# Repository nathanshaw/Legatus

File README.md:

# Legatus Hardware

This repo contains the PCB layout and schematic files for the Legatus genus.
Legatus is one of three genera developed for the Acropolis family of soundscape augmentation artefacts. Legatus specialises in loudspeaker-based cochlear soundscape augmentation.

The files were created within EAGLE CAD

The Legatus genus firmware is contained in this repo: https://github.com/nathanshaw/unified_hss_firmware

More information about this project can be found here: https://nathanvillicanashaw.com/archive
The Explorator genus can be found here: https://github.com/nathanshaw/explorator
The Speculator genus can be found here: https://github.com/nathanshaw/speculator

The following PCB design is included in this repo:
----------------------------------------------------

### Legatus major
    86mm diameter
    1x Teensy 3.2 Microcontroller
    1x power switch
    6x firmware control switches
    2x firmware control potentiometers
    10x WS2813 NeoPixel LEDs
    2x VEML 6030 Ambient Light Sensors
    1x 5v voltage regulator (D24V50F5): https://www.pololu.com/product/2851
    1x SHTC3 Temperature and Humidity Sensor
    2x onboard 18500 LiPo Batteries
    1x button controller IC
    1x audio amplifier breakout PCB
    1x SGTL5000 Breakout PCB
    2x TDK ICS-43434 MEMs microphone

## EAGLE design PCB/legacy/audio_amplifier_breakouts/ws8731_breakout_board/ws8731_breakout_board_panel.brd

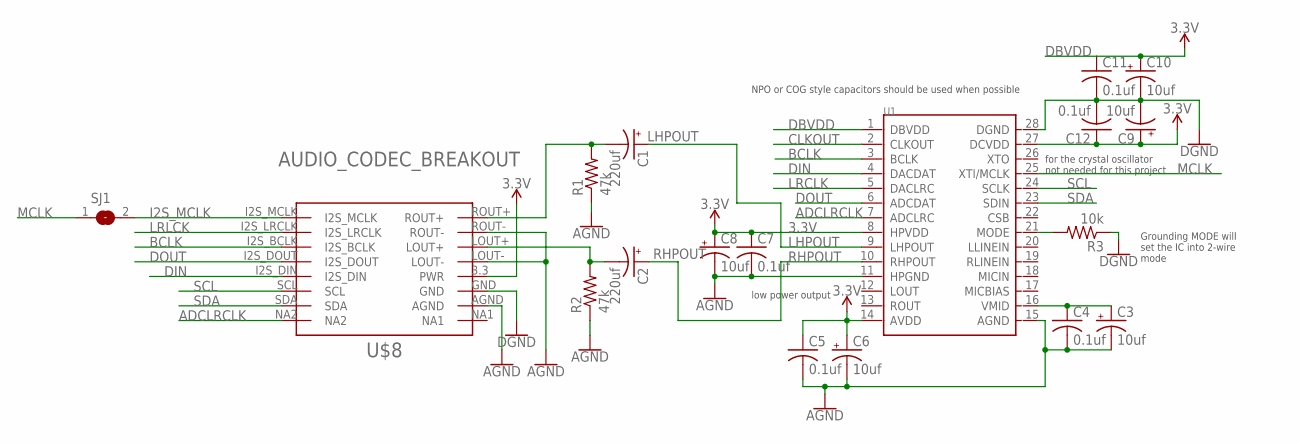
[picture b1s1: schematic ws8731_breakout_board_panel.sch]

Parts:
C1, C2: 220uf; PANASONIC_D
C3, C6, C8, C9, C10: 10uf; 153CLV-0505
C4, C5, C7, C11, C12: 0.1uf; C0805K
R1, R2: 47k; R0805
R3: 10k; R0805
SJ1: SJ
U1: CODECODER-WM8731SEDS/V(SSOP28); SSOP28-0.65-10.2X5.2MM
U$8: AUDIO_CODEC_BREAKOUT; HSS_CODEC_BREAKOUT

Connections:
3.3V: C5.1, C6.+, C7.1, C8.+, C9.+, C12.1, U1.8 (HPVDD), U1.14 (AVDD), U1.27 (DCVDD), U$8.3.3 (PWR)
ADCLRCLK: U1.7 (ADCLRC), U$8.NA2
AGND: C3.-, C4.2, C5.2, C6.-, C7.2, C8.-, R1.1, R2.1, U1.11 (HPGND), U1.15 (AGND), U$8.AGND, U$8.LOUT-, U$8.ROUT-
BCLK: U1.3 (BCLK), U$8.I2S_BCLK
CLKOUT: U1.2 (CLKOUT)
DBVDD: C10.+, C11.1, U1.1 (DBVDD)
DGND: C9.-, C10.-, C11.2, C12.2, R3.1, U1.28 (DGND)
DIN: U1.4 (DACDAT), U$8.I2S_DIN
DOUT: U1.6 (ADCDAT), U$8.I2S_DOUT
GND: U$8.GND
I2S_MCLK: SJ1.2, U$8.I2S_MCLK
LHPOUT: C1.+, U1.9 (LHPOUT)
LRCLK: U1.5 (DACLRC)
LRLCK: U$8.I2S_LRCLK
MCLK: SJ1.1, U1.25 (XTI/MCLK)
MODE: R3.2, U1.21 (MODE)
unnamed: C1.-, R1.2, U$8.ROUT+
unnamed: C2.-, R2.2, U$8.LOUT+
unnamed: C3.+, C4.1, U1.16 (VMID)
RHPOUT: C2.+, U1.10 (RHPOUT)
SCL: U1.24 (SCLK), U$8.SCL
SDA: U1.23 (SDIN), U$8.SDA

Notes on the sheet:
low power output
NPO or COG style capacitors should be used when possible
Grounding MODE will set the IC into 2-wire mode
for the crystal oscillator not needed for this project

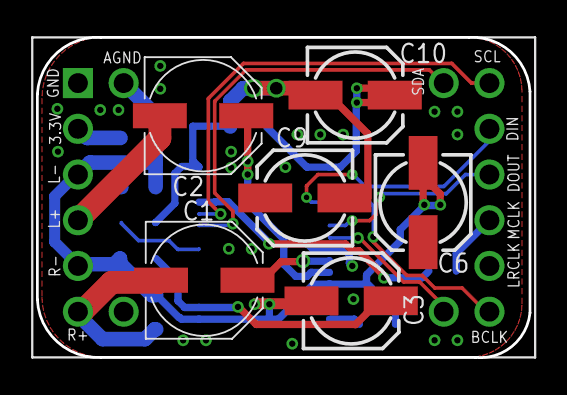
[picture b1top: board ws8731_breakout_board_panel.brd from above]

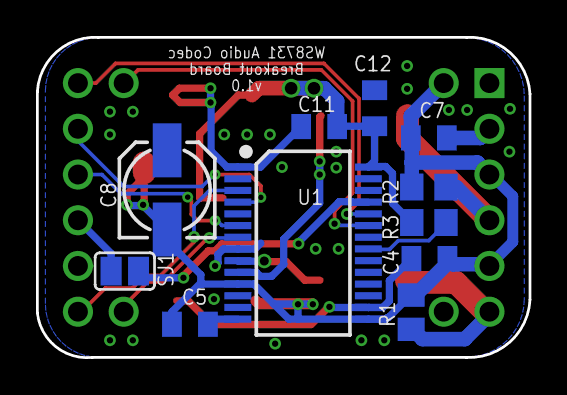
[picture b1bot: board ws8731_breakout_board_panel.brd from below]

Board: 2 copper layers, 27.4 x 17.8 mm, 18 parts (11 on the bottom side), 18 nets.

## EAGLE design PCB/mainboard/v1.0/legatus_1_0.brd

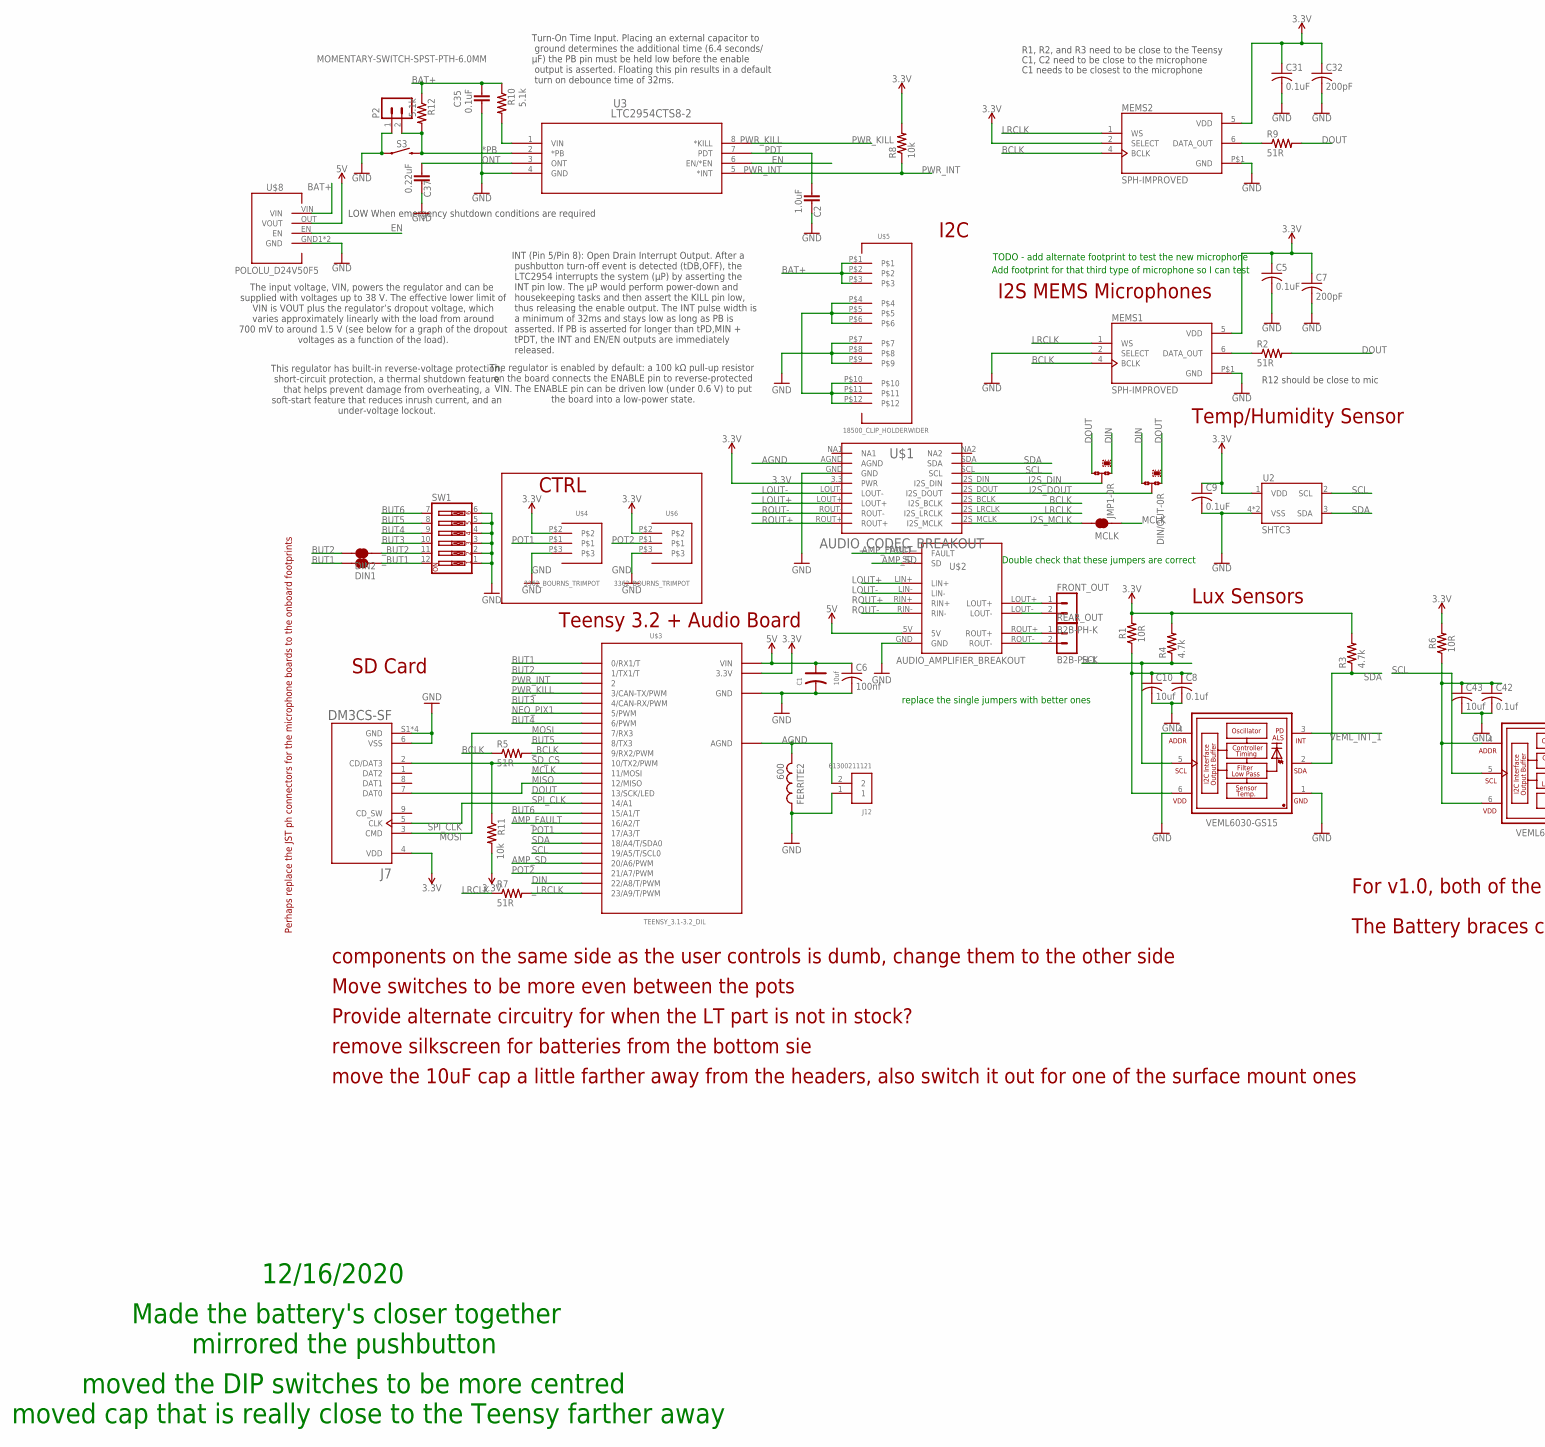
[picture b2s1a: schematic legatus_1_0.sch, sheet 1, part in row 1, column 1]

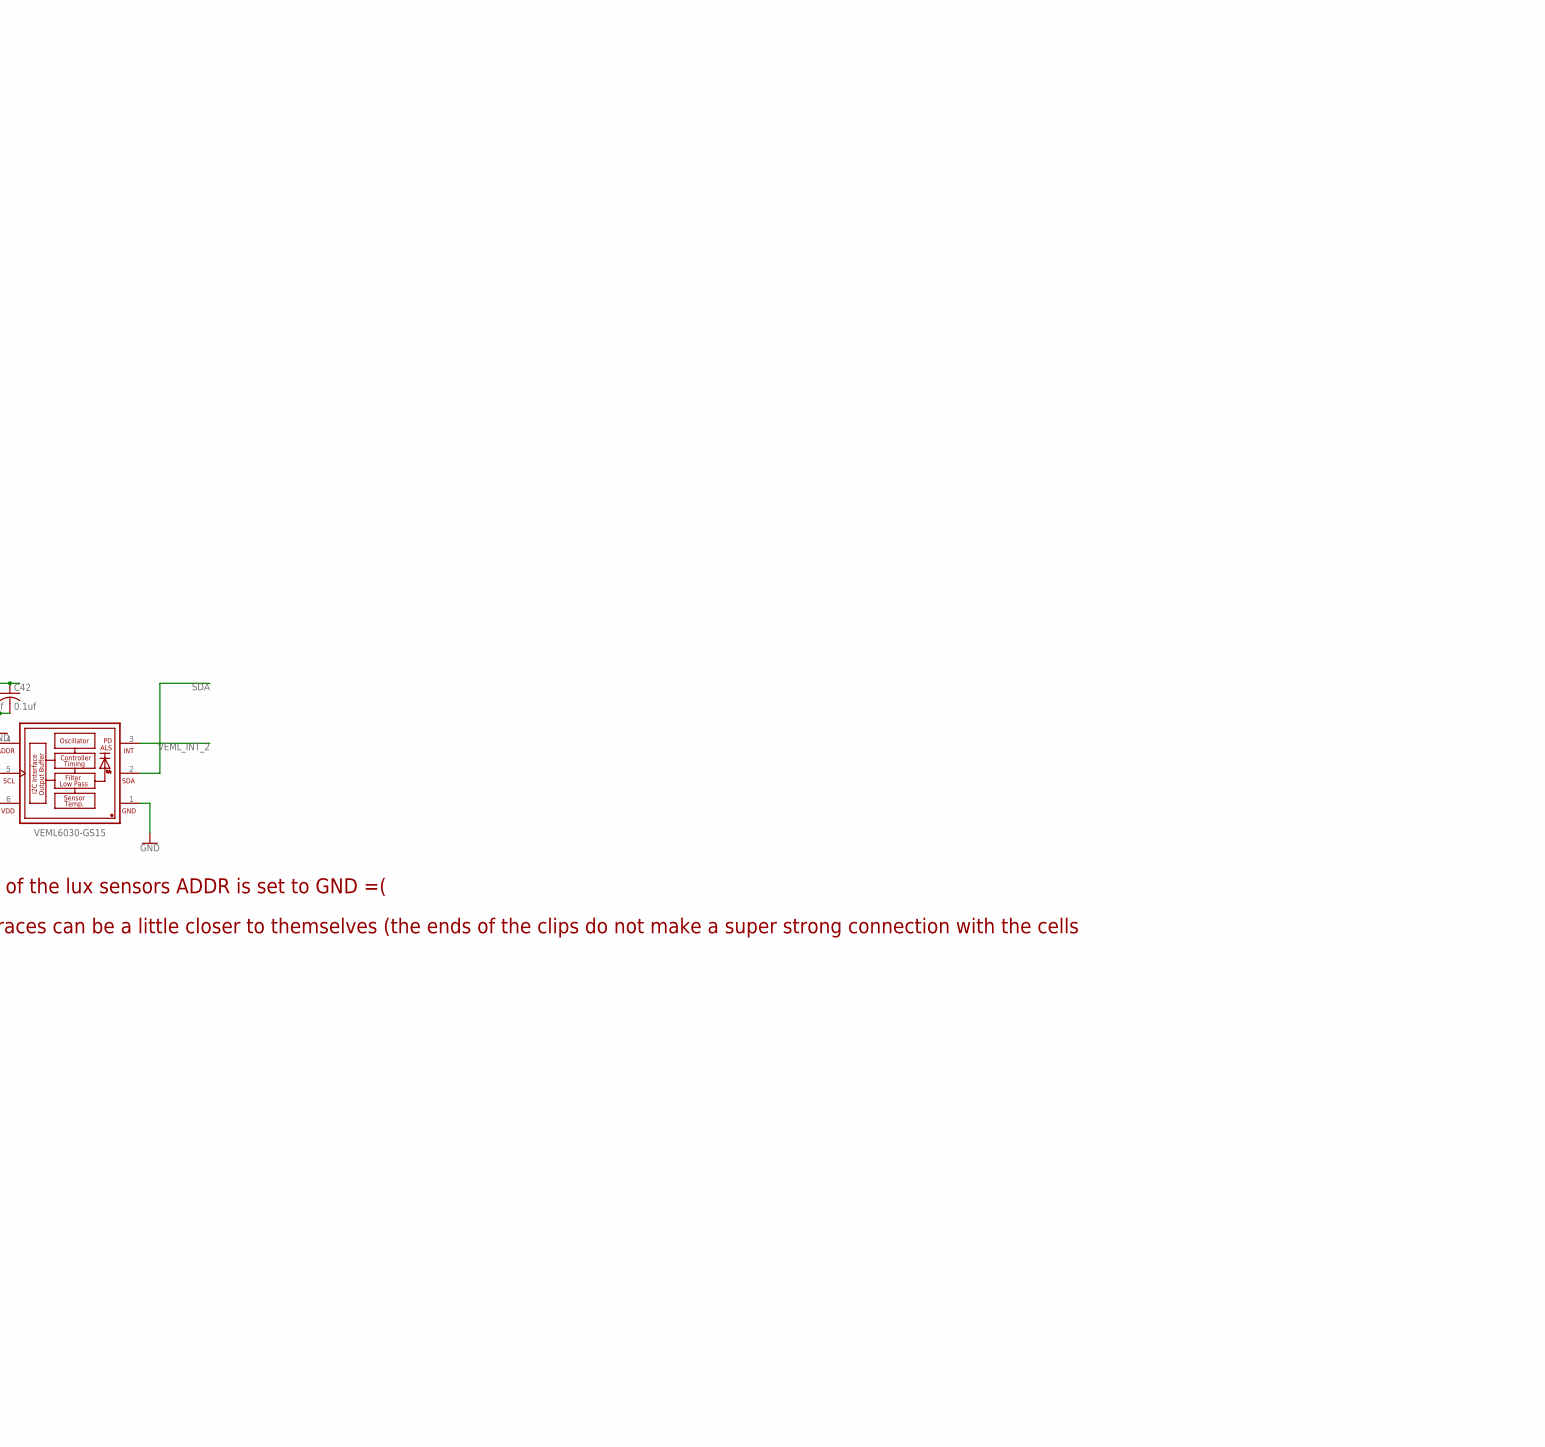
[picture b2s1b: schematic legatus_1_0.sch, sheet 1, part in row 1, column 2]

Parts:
C1: 10uf; PC-D5.3MM
C2: 1.0uF; CAPC2012X110
C5, C9, C31: 0.1uF; C0805
C6: 100nf; C2012
C7, C32: 200pF; C0805
C8, C42: 0.1uf; C0805
C10, C43: 10uf; C0805
C35: 0.1uF; CAPC2012X110
C37: 0.22uF; CAPC2012X110
DIN1, DIN2: JUMPER-SMT_2_NC_TRACE_SILK; SMT-JUMPER_2_NC_TRACE_SILK
DIN/OUT: 0R-JUMPB; B0R-JMP
FERRITE2: 600; RESC0805_N
FRONT_OUT: B2B-PH-K
J7: DM3CS-SF; HRS_DM3CS-SF
J12: 61300211121
JMP1: 0R-JUMPB; B0R-JMP
MCLK: JUMPER-SMT_2_NC_TRACE_SILK; SMT-JUMPER_2_NC_TRACE_SILK
MEMS1, MEMS2: SPH-IMPROVED; MIC_SPH0645LM4H-B_LARGER_RING
P2: B2B-PH-K
R1, R6: 10R; R0805
R2, R5, R7, R9: 51R; M0805
R3, R4: 4.7k; M0805
R8: 10k; R0805
R10, R12: 5.1k; R0805
R11: 10k; M0805
REAR_OUT: B2B-PH-K
S3: MOMENTARY-SWITCH-SPST-PTH-6.0MM; TACTILE_SWITCH_PTH_6.0MM
SW1: SW_DIP-6; EDG-06
U2: SHTC3
U3: LTC2954CTS8-2; TSOT-23_TS8
U$1: AUDIO_CODEC_BREAKOUT; HSS_CODEC_BREAKOUT
U$2: AUDIO_AMPLIFIER_BREAKOUT
U$3: TEENSY_3.1-3.2_DIL; TEENSY_3.0-3.2&LC_DIL
U$4, U$6: 3362_BOURNS_TRIMPOT
U$5: 18500_CLIP_HOLDERWIDER; 3PINBATTERY_CLIP_WIDER
U$8: POLOLU_D24V50F5
VMEL1, VMEL2: VEML6030-GS15; VISHAY_VEML6030_2X2X0.87

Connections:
3.3V: C5.1, C7.1, C9.1, C31.1, C32.1, J7.4 (VDD), MEMS1.5 (VDD), MEMS2.2 (SELECT), MEMS2.5 (VDD), R1.2, R3.2, R4.2, R6.2, R8.2, R11.2, U2.1 (VDD), U$1.3.3 (PWR), U$3.3.3V, U$4.P$2, U$6.P$2
5V: C1.+, C6.1, U$2.5V, U$3.VIN, U$8.OUT (VOUT); also elsewhere on the board
*PB: P2.2, R12.2, S3.3 (2), U3.2 (*PB)
AGND: FERRITE2.2, J12.2, U$1.AGND, U$3.AGND
AMP_FAULT: U$2.FAULT, U$3.16/A2 (16/A2/T)
AMP_SD: U$2.SD, U$3.20/A6 (20/A6/PWM)
BAT+: C35.1, R10.1, R12.1, U$5.P$1, U$5.P$2, U$5.P$3, U$8.VIN
BCLK: MEMS1.4 (BCLK), MEMS2.4 (BCLK), R5.1, U$1.I2S_BCLK
BUT1: DIN1.1, U$3.0 (0/RX1/T)
BUT2: DIN2.1, U$3.1 (1/TX1/T)
BUT3: SW1.10, U$3.4 (4/CAN-RX/PWM)
BUT4: SW1.9, U$3.6 (6/PWM)
BUT5: SW1.8, U$3.8 (8/TX3)
BUT6: SW1.7, U$3.15/A1 (15/A1/T)
DIN: DIN/OUT.3, JMP1.1, U$3.22/A8 (22/A8/T/PWM)
DOUT: DIN/OUT.1, JMP1.3, R2.2, R9.2, U$3.13 (13/SCK/LED)
EN: U3.6 (EN/*EN), U$8.EN
GND: C1.-, C2.2, C5.2, C6.2, C7.2, C8.2, C9.2, C10.2, C31.2, C32.2, C35.2, C37.2, C42.2, C43.2, FERRITE2.1, J7.6 (VSS), J7.S1 (GND), J7.S2 (GND), J7.S3 (GND), J7.S5 (GND), J12.1, MEMS1.2 (SELECT), MEMS1.P$1 (GND), MEMS2.P$1 (GND), P2.1, S3.1, SW1.1, SW1.2, SW1.3, SW1.4, SW1.5, SW1.6, U2.4 (VSS), U2.5 (VSS), U3.4 (GND), U$1.GND, U$2.GND, U$3.GND, U$4.P$3, U$5.P$7, U$5.P$8, U$5.P$9, U$6.P$3, U$8.GND1 (GND), U$8.GND2 (GND), VMEL1.1 (GND), VMEL1.4 (ADDR), VMEL2.1 (GND); also elsewhere on the board
I2S_DIN: JMP1.2, U$1.I2S_DIN
I2S_DOUT: DIN/OUT.2, U$1.I2S_DOUT
I2S_MCLK: MCLK.1, U$1.I2S_MCLK
LOUT+: U$1.LOUT+, U$2.LIN+
LOUT-: U$1.LOUT-, U$2.LIN-
LRCLK: MEMS1.1 (WS), MEMS2.1 (WS), R7.1, U$1.I2S_LRCLK
MCLK: MCLK.2, U$3.11 (11/MOSI)
MISO: J7.7 (DAT0), U$3.12 (12/MISO)
MOSI: J7.3 (CMD), U$3.7 (7/RX3)
unnamed: MEMS1.6 (DATA_OUT), R2.1
unnamed: U$5.P$4, U$5.P$5, U$5.P$6, U$5.P$10, U$5.P$11, U$5.P$12
unnamed: C42.1, C43.1, R6.1, VMEL2.4 (ADDR), VMEL2.6 (VDD)
unnamed: C8.1, C10.1, R1.1, VMEL1.6 (VDD)
unnamed: R10.2, U3.1 (VIN)
unnamed: MEMS2.6 (DATA_OUT), R9.1
unnamed: REAR_OUT.2, U$2.ROUT-
unnamed: REAR_OUT.1, U$2.ROUT+
unnamed: FRONT_OUT.2, U$2.LOUT-
unnamed: FRONT_OUT.1, U$2.LOUT+
NEO_PIX1: U$3.5 (5/PWM); also elsewhere on the board
ONT: C37.1, U3.3 (ONT)
PDT: C2.1, U3.7 (PDT)
POT1: U$3.17/A3 (17/A3/T), U$4.P$1
POT2: U$3.21/A7 (21/A7/PWM), U$6.P$1
PWR_INT: R8.1, U3.5 (*INT), U$3.2
PWR_KILL: U3.8 (*KILL), U$3.3 (3/CAN-TX/PWM)
ROUT+: U$1.ROUT+, U$2.RIN+
ROUT-: U$1.ROUT-, U$2.RIN-
SCL: R4.1, U2.2 (SCL), U$1.SCL, U$3.19/A5 (19/A5/T/SCL0), VMEL1.5 (SCL), VMEL2.5 (SCL)
SDA: R3.1, U2.3 (SDA), U$1.SDA, U$3.18/A4 (18/A4/T/SDA0), VMEL1.2 (SDA), VMEL2.2 (SDA)
SD_CS: J7.2 (CD/DAT3), R11.1, U$3.10 (10/TX2/PWM)
SPI_CLK: J7.5 (CLK), U$3.14/A0 (14/A1)
VEML_INT_1: VMEL1.3 (INT)
VEML_INT_2: VMEL2.3 (INT)
_BCLK: R5.2, U$3.9 (9/RX2/PWM)
_BUT1: DIN1.2, SW1.12
_BUT2: DIN2.2, SW1.11
_LRCLK: R7.2, U$3.23/A9 (23/A9/T/PWM)

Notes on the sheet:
I2C
Teensy 3.2 + Audio Board
CTRL
Perhaps replace the JST ph connectors for the microphone boards to the onboard footprints
I2S MEMS Microphones
R12 should be close to mic
Temp/Humidity Sensor
10R
Lux Sensors
SD Card
Add footprint for that third type of microphone so I can test
R1, R2, and R3 need to be close to the Teensy
C1, C2 need to be close to the microphone
C1 needs to be closest to the microphone
This regulator has built-in reverse-voltage protection, short-circuit protection, a thermal shutdown feature that helps prevent damage from overheating, a soft-start feature that reduces inrush current, and an under-voltage lockout.
The input voltage, VIN, powers the regulator and can be supplied with voltages up to 38 V. The effective lower limit of VIN is VOUT plus the regulator’s dropout voltage, which varies approximately linearly with the load from around 700 mV to around 1.5 V (see below for a graph of the dropout voltag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
The regulator is enabled by default: a 100 kΩ pull-up resistor on the board connects the ENABLE pin to reverse-protected VIN. The ENABLE pin can be driven low (under 0.6 V) to put the board into a low-power state.
LOW When emergency shutdown conditions are required
Turn-On Time Input. Placing an external capacitor to ground determines the additional time (6.4 seconds/ μF) the PB pin must be held low before the enable output is asserted. Floating this pin results in a default turn on debounce time of 32ms.
INT (Pin 5/Pin 8): Open Drain Interrupt Output. After a pushbutton turn-off event is detected (tDB,OFF), the LTC2954 interrupts the system (μP) by asserting the INT pin low. The μP would perform power-down and housekeeping tasks and then assert the KILL pin low, thus releasing the enable output. Th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
TODO - add alternate footprint to test the new microphone
Double check that these jumpers are correct
replace the single jumpers with better ones
components on the same side as the user controls is dumb, change them to the other side
Move switches to be more even between the pots
remove silkscreen for batteries from the bottom sie
move the 10uF cap a little farther away from the headers, also switch it out for one of the surface mount ones
Provide alternate circuitry for when the LT part is not in stock?
For v1.0, both of the lux sensors ADDR is set to GND =(
The Battery braces can be a little closer to themselves (the ends of the clips do not make a super strong connection with the cells
Made the battery's closer together
12/16/2020
mirrored the pushbutton
moved the DIP switches to be more centred
moved cap that is really close to the Teensy farther away

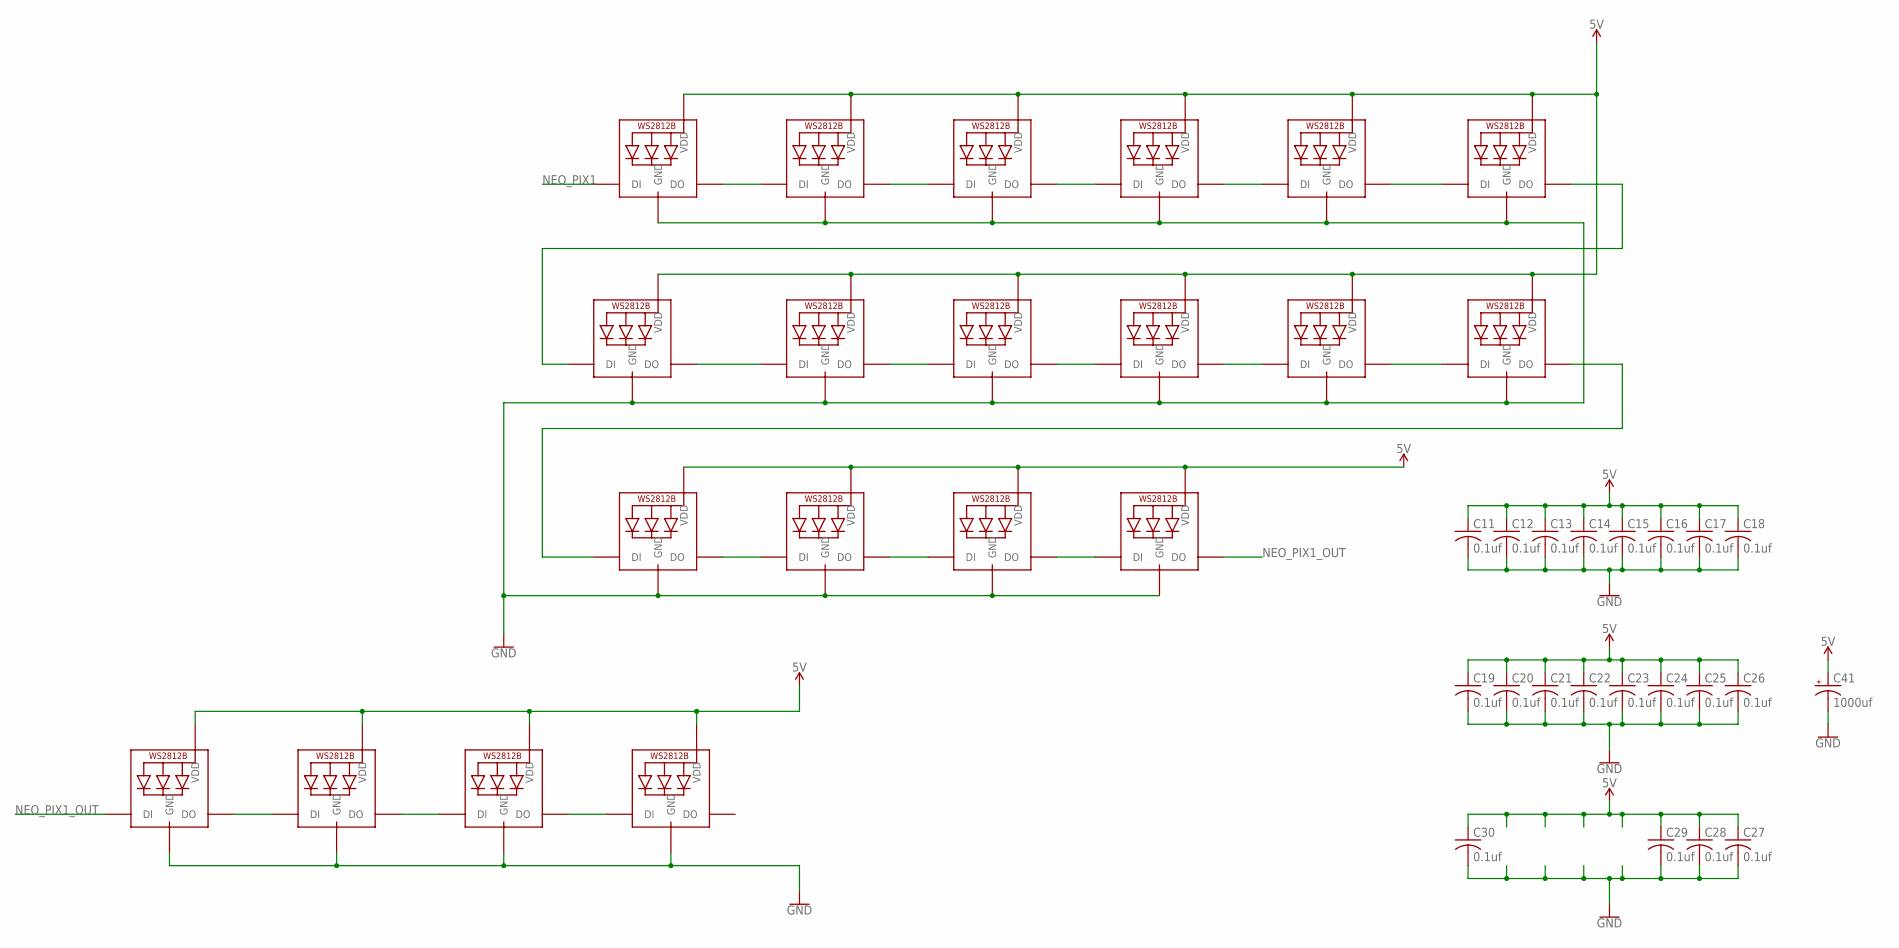
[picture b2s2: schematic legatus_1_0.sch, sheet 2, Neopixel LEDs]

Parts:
C11, C12, C13, C14, C15, C16, C17, C18, C19, C20, C21, C22, C23, C24, C25, C26, C27, C28, C29, C30: 0.1uf; C0805
C41: 1000uf; 153CLV-1010
LED1, LED2, LED3, LED4, LED5, LED6, LED7, LED8, LED9, LED10, LED11, LED12, LED13, LED14, LED15, LED16, LED17, LED18, LED19, LED20: WS2812B_5050N; WS2812B-NARROW

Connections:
5V: C11.1, C12.1, C13.1, C14.1, C15.1, C16.1, C17.1, C18.1, C19.1, C20.1, C21.1, C22.1, C23.1, C24.1, C25.1, C26.1, C27.1, C28.1, C29.1, C30.1, C41.+, LED1.1-VDD (VDD), LED2.1-VDD (VDD), LED3.1-VDD (VDD), LED4.1-VDD (VDD), LED5.1-VDD (VDD), LED6.1-VDD (VDD), LED7.1-VDD (VDD), LED8.1-VDD (VDD), LED9.1-VDD (VDD), LED10.1-VDD (VDD), LED11.1-VDD (VDD), LED12.1-VDD (VDD), LED13.1-VDD (VDD), LED14.1-VDD (VDD), LED15.1-VDD (VDD), LED16.1-VDD (VDD), LED17.1-VDD (VDD), LED18.1-VDD (VDD), LED19.1-VDD (VDD), LED20.1-VDD (VDD); also elsewhere on the board
GND: C11.2, C12.2, C13.2, C14.2, C15.2, C16.2, C17.2, C18.2, C19.2, C20.2, C21.2, C22.2, C23.2, C24.2, C25.2, C26.2, C27.2, C28.2, C29.2, C30.2, C41.-, LED1.3-GND (GND), LED2.3-GND (GND), LED3.3-GND (GND), LED4.3-GND (GND), LED5.3-GND (GND), LED6.3-GND (GND), LED7.3-GND (GND), LED8.3-GND (GND), LED9.3-GND (GND), LED10.3-GND (GND), LED11.3-GND (GND), LED12.3-GND (GND), LED13.3-GND (GND), LED14.3-GND (GND), LED15.3-GND (GND), LED16.3-GND (GND), LED17.3-GND (GND), LED18.3-GND (GND), LED19.3-GND (GND), LED20.3-GND (GND); also elsewhere on the board
unnamed: LED1.2-DOUT (DO), LED2.4-DIN (DI)
unnamed: LED2.2-DOUT (DO), LED3.4-DIN (DI)
unnamed: LED3.2-DOUT (DO), LED4.4-DIN (DI)
unnamed: LED4.2-DOUT (DO), LED5.4-DIN (DI)
unnamed: LED5.2-DOUT (DO), LED6.4-DIN (DI)
unnamed: LED7.2-DOUT (DO), LED8.4-DIN (DI)
unnamed: LED8.2-DOUT (DO), LED9.4-DIN (DI)
unnamed: LED9.2-DOUT (DO), LED10.4-DIN (DI)
unnamed: LED10.2-DOUT (DO), LED11.4-DIN (DI)
unnamed: LED11.2-DOUT (DO), LED12.4-DIN (DI)
unnamed: LED13.2-DOUT (DO), LED14.4-DIN (DI)
unnamed: LED14.2-DOUT (DO), LED15.4-DIN (DI)
unnamed: LED15.2-DOUT (DO), LED16.4-DIN (DI)
unnamed: LED12.2-DOUT (DO), LED13.4-DIN (DI)
unnamed: LED6.2-DOUT (DO), LED7.4-DIN (DI)
unnamed: LED18.2-DOUT (DO), LED19.4-DIN (DI)
unnamed: LED19.2-DOUT (DO), LED20.4-DIN (DI)
unnamed: LED17.2-DOUT (DO), LED18.4-DIN (DI)
NEO_PIX1: LED1.4-DIN (DI); also elsewhere on the board
NEO_PIX1_OUT: LED16.2-DOUT (DO), LED17.4-DIN (DI)

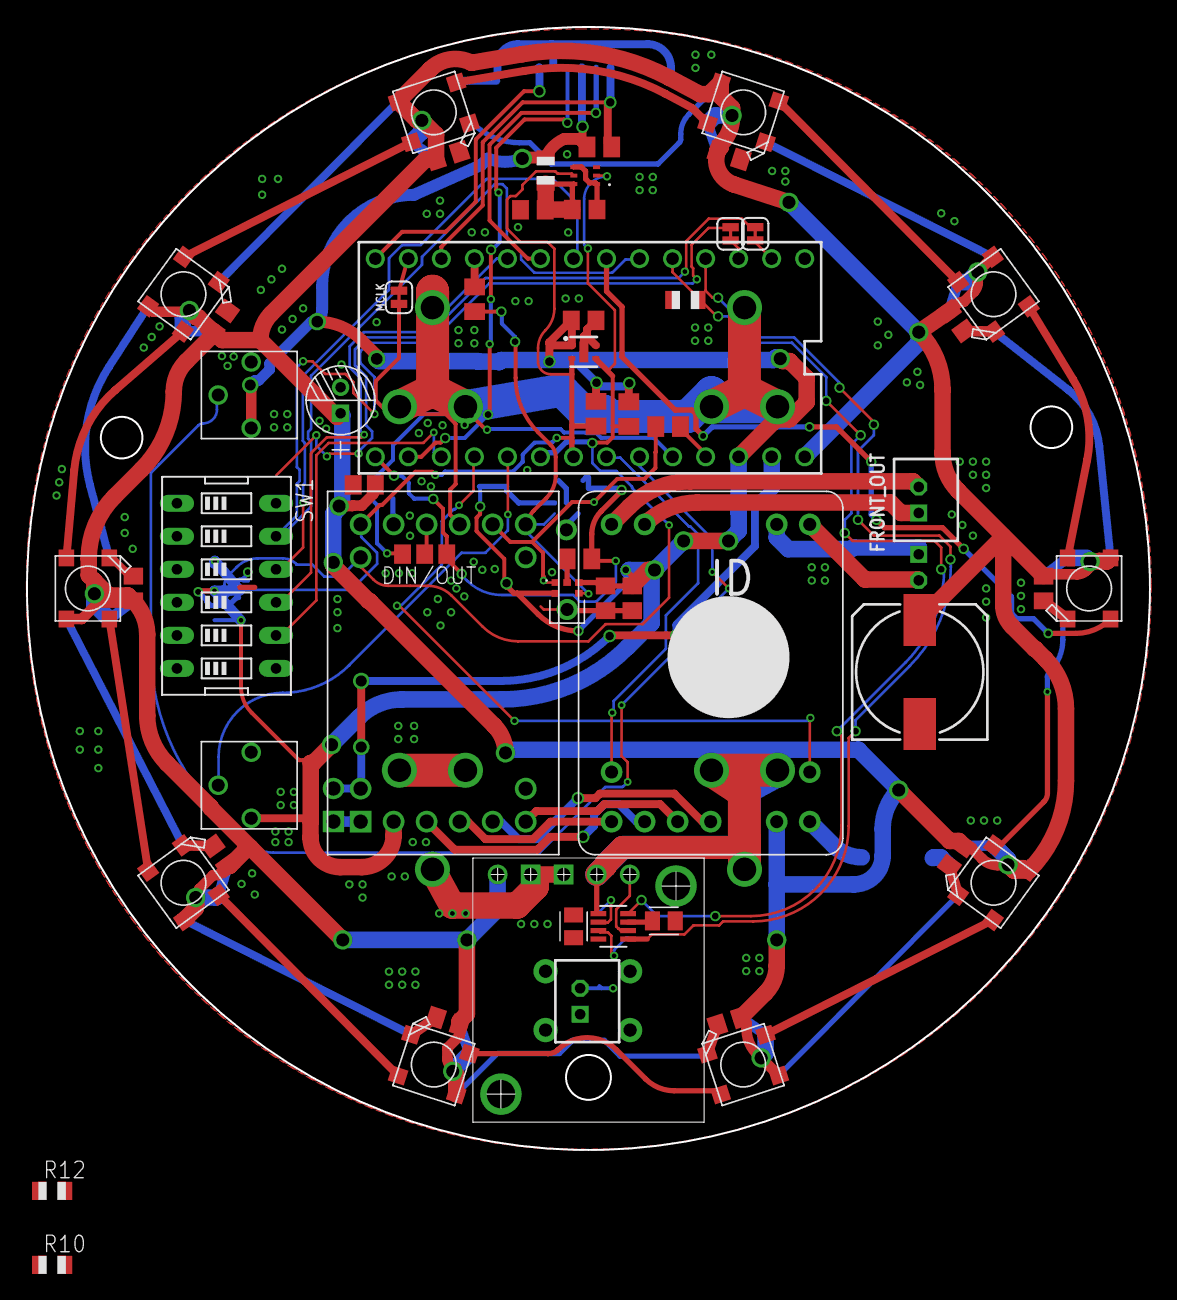
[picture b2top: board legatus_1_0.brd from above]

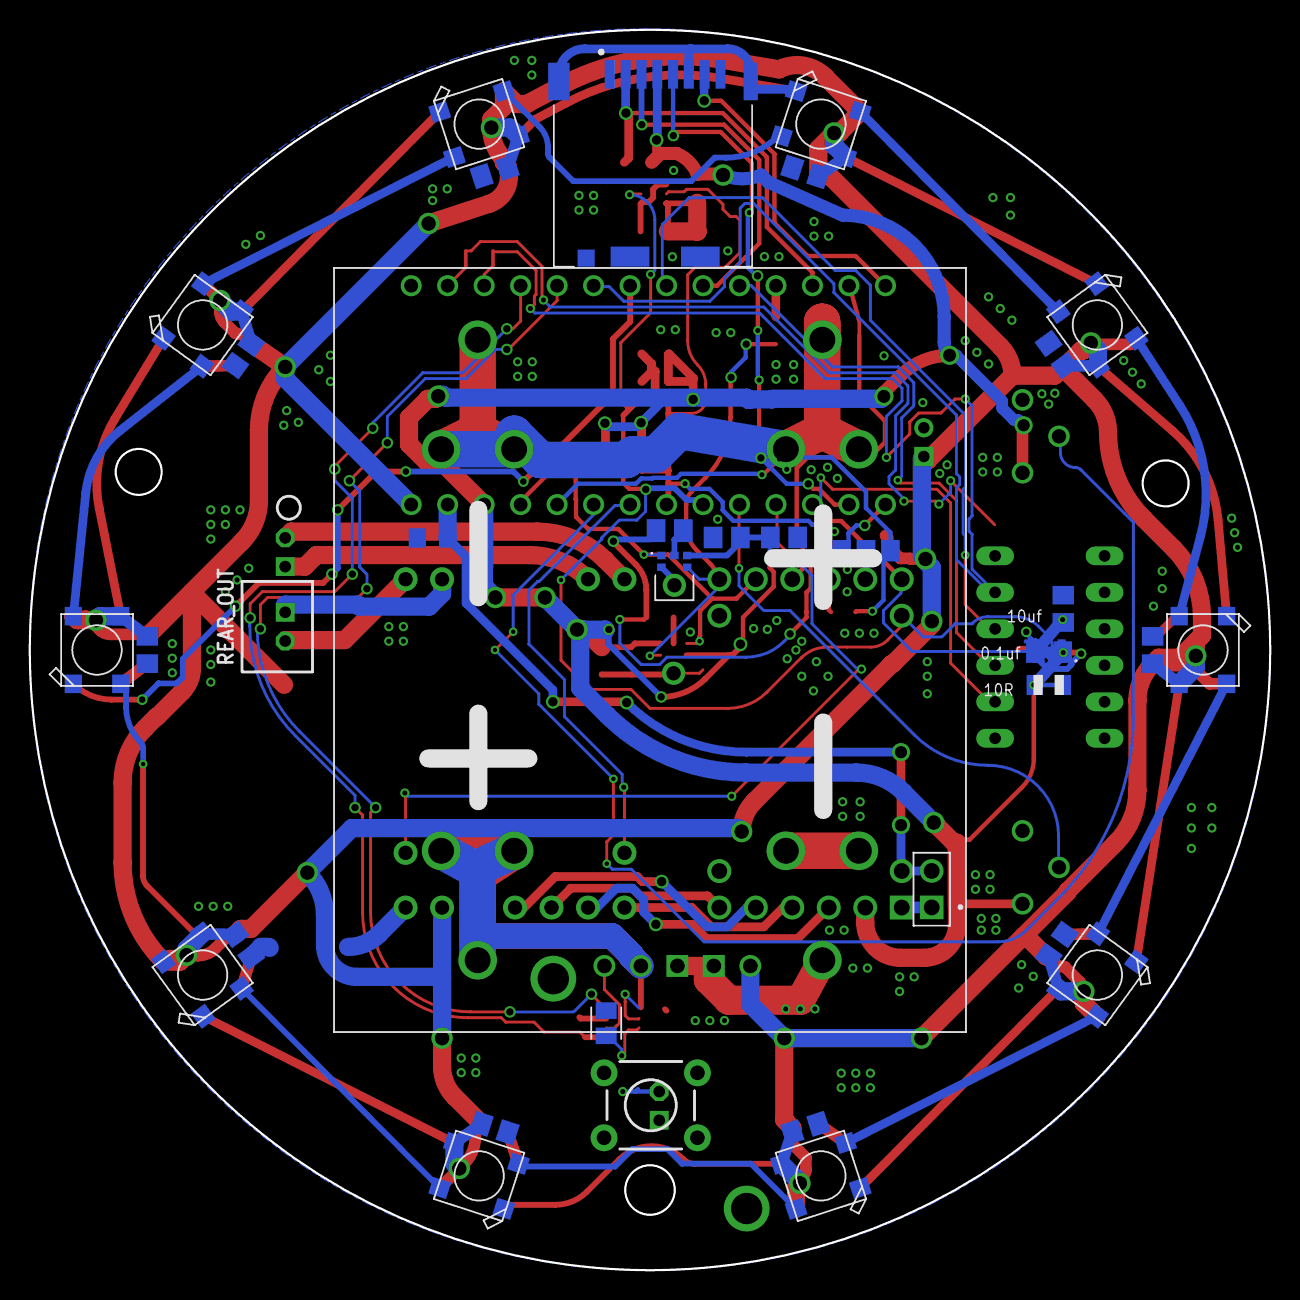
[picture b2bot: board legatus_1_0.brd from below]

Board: 2 copper layers, 86.4 x 86.4 mm, 93 parts (36 on the bottom side), 73 nets.

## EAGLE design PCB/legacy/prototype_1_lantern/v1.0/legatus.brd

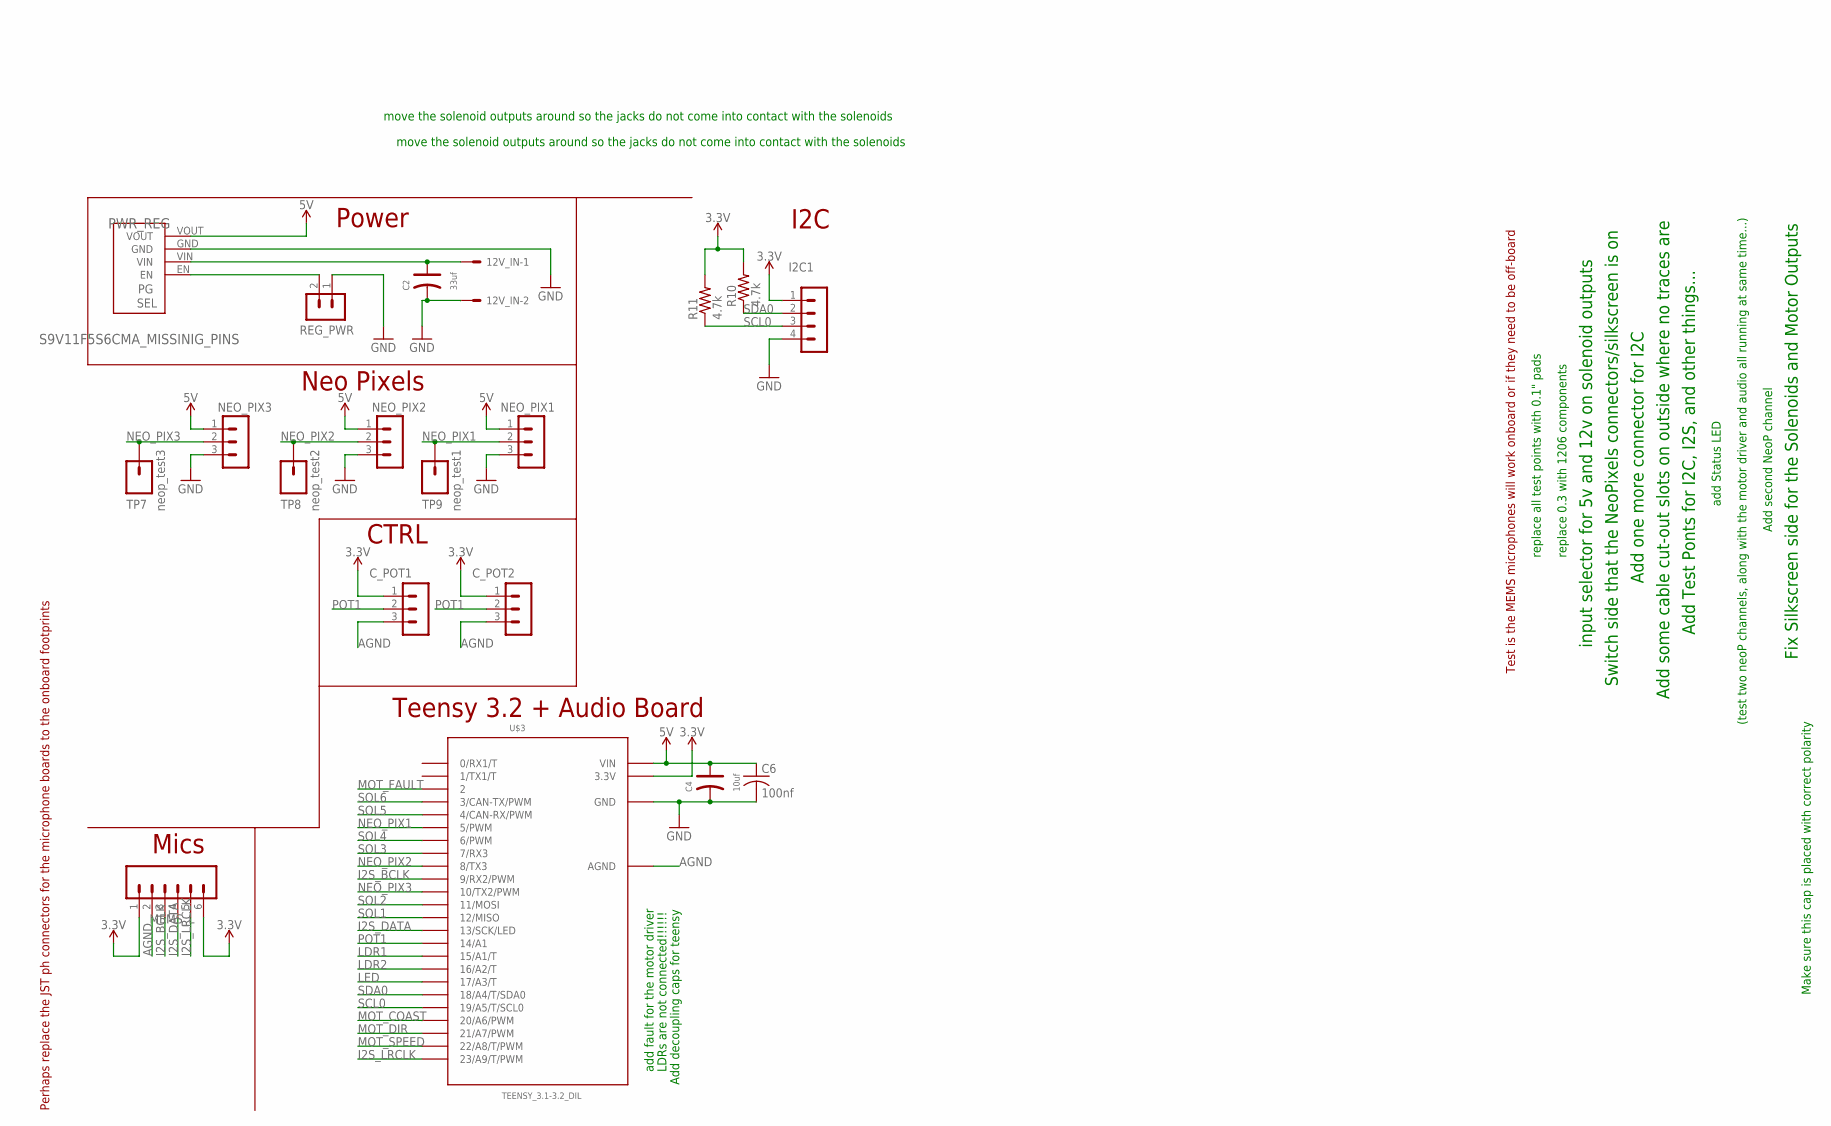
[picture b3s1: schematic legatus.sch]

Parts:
12V_IN: 5566-2
C2: 33uf; PC-D5.3MM
C4: 10uf; PC-D5.3MM
C6: 100nf; C2012
C_POT1, C_POT2: B3B-PH-K
I2C1: B4B-PH-K
MEMS_L: CONN_06POLAR; MOLEX-1X6
NEO_PIX1, NEO_PIX2, NEO_PIX3: B3B-PH-K
PWR_REG: S9V11F5S6CMA_MISSINIG_PINS; S9V11F3S5CMA_MISSING_PINS
R10, R11: 4.7k; M1206
REG_PWR: B2B-PH-K
TP7: neop_test3; 1X01
TP8: neop_test2; 1X01
TP9: neop_test1; 1X01
U$3: TEENSY_3.1-3.2_DIL; TEENSY_3.0-3.2&LC_DIL

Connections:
3.3V: C_POT1.1, C_POT2.1, I2C1.1, MEMS_L.1, MEMS_L.6, R10.2, R11.2, U$3.3.3V
5V: C4.+, C6.1, NEO_PIX1.1, NEO_PIX2.1, NEO_PIX3.1, PWR_REG.VOUT, U$3.VIN
12V: 12V_IN.1, C2.+, PWR_REG.VIN
AGND: C_POT1.3, C_POT2.3, MEMS_L.2, U$3.AGND
GND: 12V_IN.2, C2.-, C4.-, C6.2, I2C1.4, NEO_PIX1.3, NEO_PIX2.3, NEO_PIX3.3, PWR_REG.GND, REG_PWR.1, U$3.GND
I2S_BCLK: MEMS_L.3, U$3.9 (9/RX2/PWM)
I2S_DATA: MEMS_L.4, U$3.13 (13/SCK/LED)
I2S_LRCLK: MEMS_L.5, U$3.23/A9 (23/A9/T/PWM)
LDR1: U$3.15/A1 (15/A1/T)
LDR2: U$3.16/A2 (16/A2/T)
LED: U$3.17/A3 (17/A3/T)
MOT_COAST: U$3.20/A6 (20/A6/PWM)
MOT_DIR: U$3.21/A7 (21/A7/PWM)
MOT_FAULT: U$3.2
MOT_SPEED: U$3.22/A8 (22/A8/T/PWM)
unnamed: PWR_REG.EN, REG_PWR.2
NEO_PIX1: NEO_PIX1.2, TP9.1, U$3.5 (5/PWM)
NEO_PIX2: NEO_PIX2.2, TP8.1, U$3.8 (8/TX3)
NEO_PIX3: NEO_PIX3.2, TP7.1, U$3.10 (10/TX2/PWM)
POT1: C_POT1.2, C_POT2.2, U$3.14/A0 (14/A1)
SCL0: I2C1.3, R11.1, U$3.19/A5 (19/A5/T/SCL0)
SDA0: I2C1.2, R10.1, U$3.18/A4 (18/A4/T/SDA0)
SOL1: U$3.12 (12/MISO)
SOL2: U$3.11 (11/MOSI)
SOL3: U$3.7 (7/RX3)
SOL4: U$3.6 (6/PWM)
SOL5: U$3.4 (4/CAN-RX/PWM)
SOL6: U$3.3 (3/CAN-TX/PWM)

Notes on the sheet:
Neo Pixels
I2C
Teensy 3.2 + Audio Board
Mics
Power
Make sure this cap is placed with correct polarity
CTRL
add fault for the motor driver
LDRs are not connected!!!!!!
Fix Silkscreen side for the Solenoids and Motor Outputs
Add Test Ponts for I2C, I2S, and other things...
Add some cable cut-out slots on outside where no traces are
Add one more connector for I2C
Switch side that the NeoPixels connectors/silkscreen is on
input selector for 5v and 12v on solenoid outputs
Add second NeoP channel
(test two neoP channels, along with the motor driver and audio all running at same time...)
add Status LED
replace 0.3 with 1206 components
replace all test points with 0.1" pads
Add decoupling caps for teensy
Test is the MEMS microphones will work onboard or if they need to be off-board
Perhaps replace the JST ph connectors for the microphone boards to the onboard footprints
move the solenoid outputs around so the jacks do not come into contact with the solenoids

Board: 2 copper layers, 19 parts (0 on the bottom side), 15 nets, no tracks yet.

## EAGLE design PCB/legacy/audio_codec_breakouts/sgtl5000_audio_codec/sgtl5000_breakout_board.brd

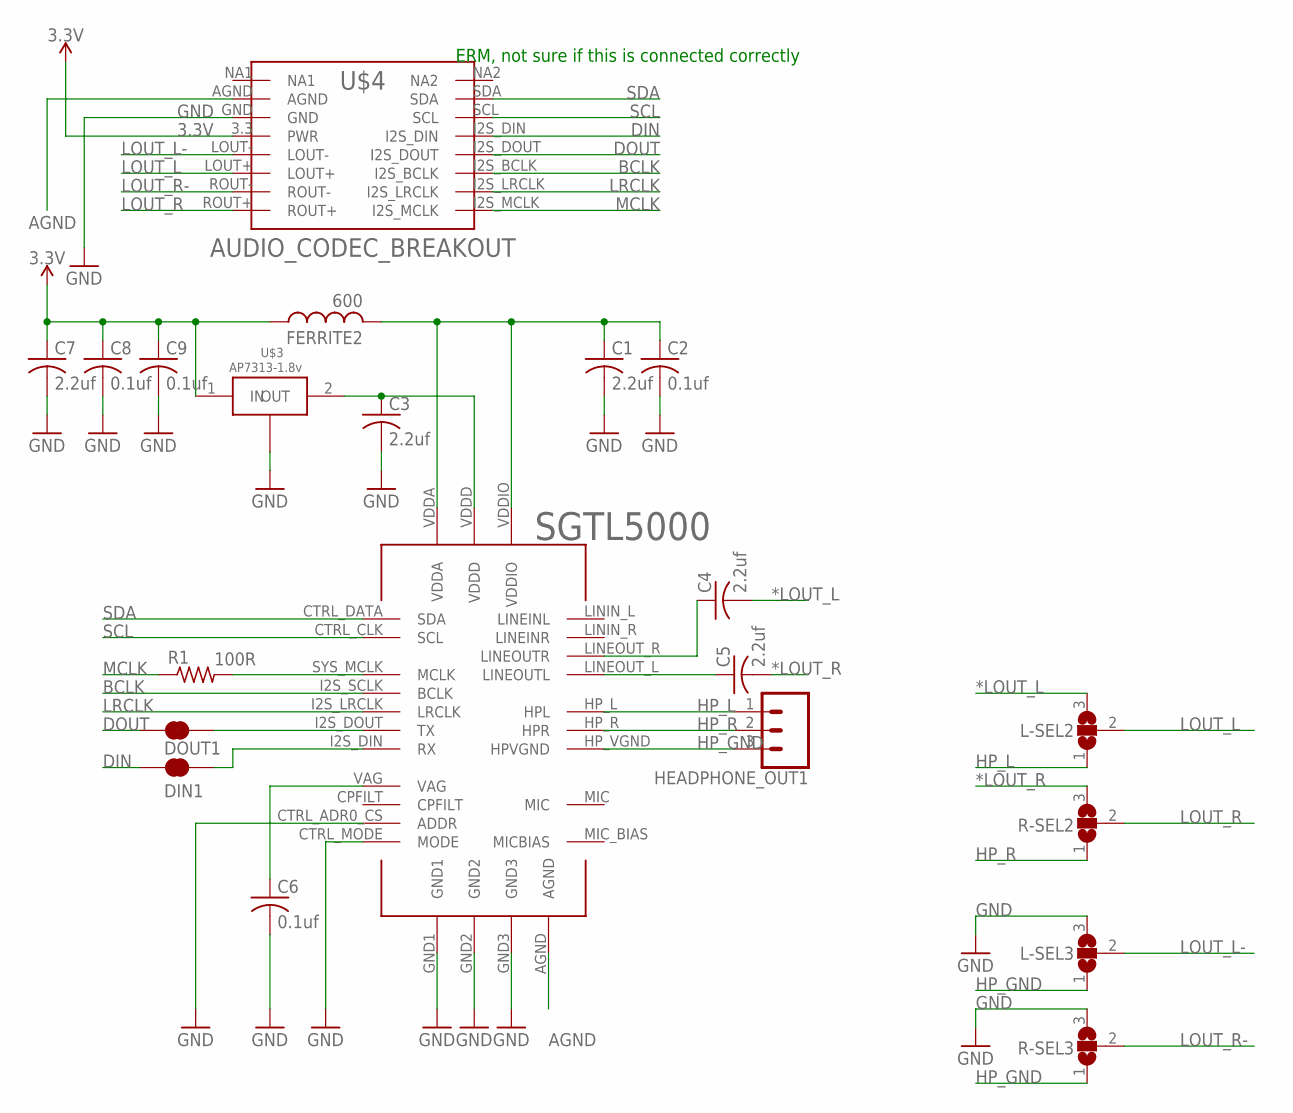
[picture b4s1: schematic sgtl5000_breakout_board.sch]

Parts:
C1, C3, C4, C5, C7: 2.2uf; C0805
C2, C6, C8, C9: 0.1uf; C0805
DIN1: JUMPER-SMT_2_NC_TRACE_SILK; SMT-JUMPER_2_NC_TRACE_SILK
DOUT1: JUMPER-SMT_2_NC_TRACE_SILK; SMT-JUMPER_2_NC_TRACE_SILK
FERRITE2: 600; RESC0805_N
HEADPHONE_OUT1: CONN_03; 1X03
L-SEL2, L-SEL3: SJ2W; SJ_2
R1: 100R; M0805
R-SEL2, R-SEL3: SJ2W; SJ_2
U$2: SGTL5000; QFN-32-5X5MM
U$3: AP7313-1.8v; SOT-23
U$4: AUDIO_CODEC_BREAKOUT; HSS_CODEC_BREAKOUT

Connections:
3.3V: C7.1, C8.1, C9.1, FERRITE2.1, U$3.1 (IN), U$4.3.3 (PWR)
*LOUT_L: C4.2, L-SEL2.3
*LOUT_R: C5.2, R-SEL2.3
AGND: U$2.AGND, U$4.AGND
BCLK: U$2.I2S_SCLK (BCLK), U$4.I2S_BCLK
DIN: DIN1.1, U$4.I2S_DIN
DOUT: DOUT1.1, U$4.I2S_DOUT
EDITROUTE1: C1.1, C2.1, FERRITE2.2, U$2.VDDA, U$2.VDDIO
GND: C1.2, C2.2, C3.2, C6.2, C7.2, C8.2, C9.2, L-SEL3.3, R-SEL3.3, U$2.CTRL_ADR0_CS (ADDR), U$2.CTRL_MODE (MODE), U$2.GND1, U$2.GND2, U$2.GND3, U$3.3 (GND), U$4.GND
HP_GND: HEADPHONE_OUT1.3, L-SEL3.1, R-SEL3.1, U$2.HP_VGND (HPVGND)
HP_L: HEADPHONE_OUT1.1, L-SEL2.1, U$2.HP_L (HPL)
HP_R: HEADPHONE_OUT1.2, R-SEL2.1, U$2.HP_R (HPR)
LOUT_L: L-SEL2.2, U$4.LOUT+
LOUT_L-: L-SEL3.2, U$4.LOUT-
LOUT_R: R-SEL2.2, U$4.ROUT+
LOUT_R-: R-SEL3.2, U$4.ROUT-
LRCLK: U$2.I2S_LRCLK (LRCLK), U$4.I2S_LRCLK
MCLK: R1.1, U$4.I2S_MCLK
unnamed: C4.1, U$2.LINEOUT_R (LINEOUTR)
unnamed: C5.1, U$2.LINEOUT_L (LINEOUTL)
unnamed: C6.1, U$2.VAG
unnamed: DIN1.2, U$2.I2S_DIN (RX)
unnamed: DOUT1.2, U$2.I2S_DOUT (TX)
unnamed: R1.2, U$2.SYS_MCLK (MCLK)
unnamed: C3.1, U$2.VDDD, U$3.2 (OUT)
SCL: U$2.CTRL_CLK (SCL), U$4.SCL
SDA: U$2.CTRL_DATA (SDA), U$4.SDA

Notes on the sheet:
ERM, not sure if this is connected correctly

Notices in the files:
parts and their libraries:
con-jst-ph: Copyright (C) 2016, Bob Starr
SparkFun-PowerSymbols: Licensing: Creative Commons ShareAlike 4.0 International - https://creativecommons.org/licenses/by-sa/4.0
